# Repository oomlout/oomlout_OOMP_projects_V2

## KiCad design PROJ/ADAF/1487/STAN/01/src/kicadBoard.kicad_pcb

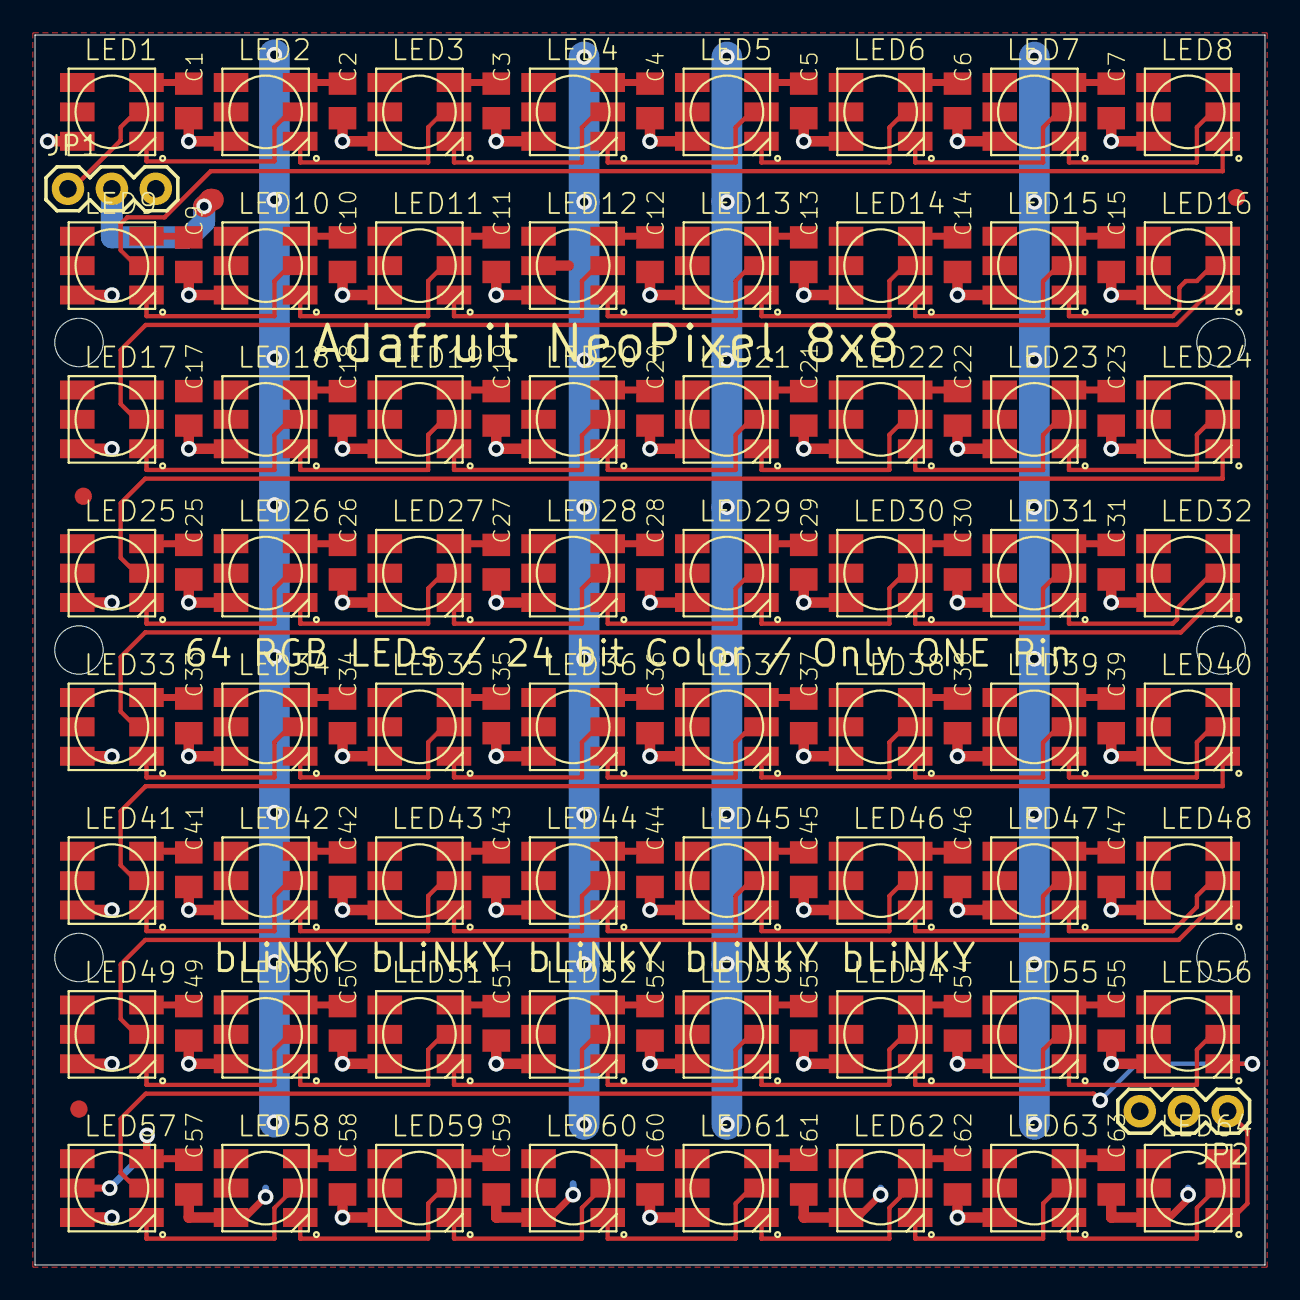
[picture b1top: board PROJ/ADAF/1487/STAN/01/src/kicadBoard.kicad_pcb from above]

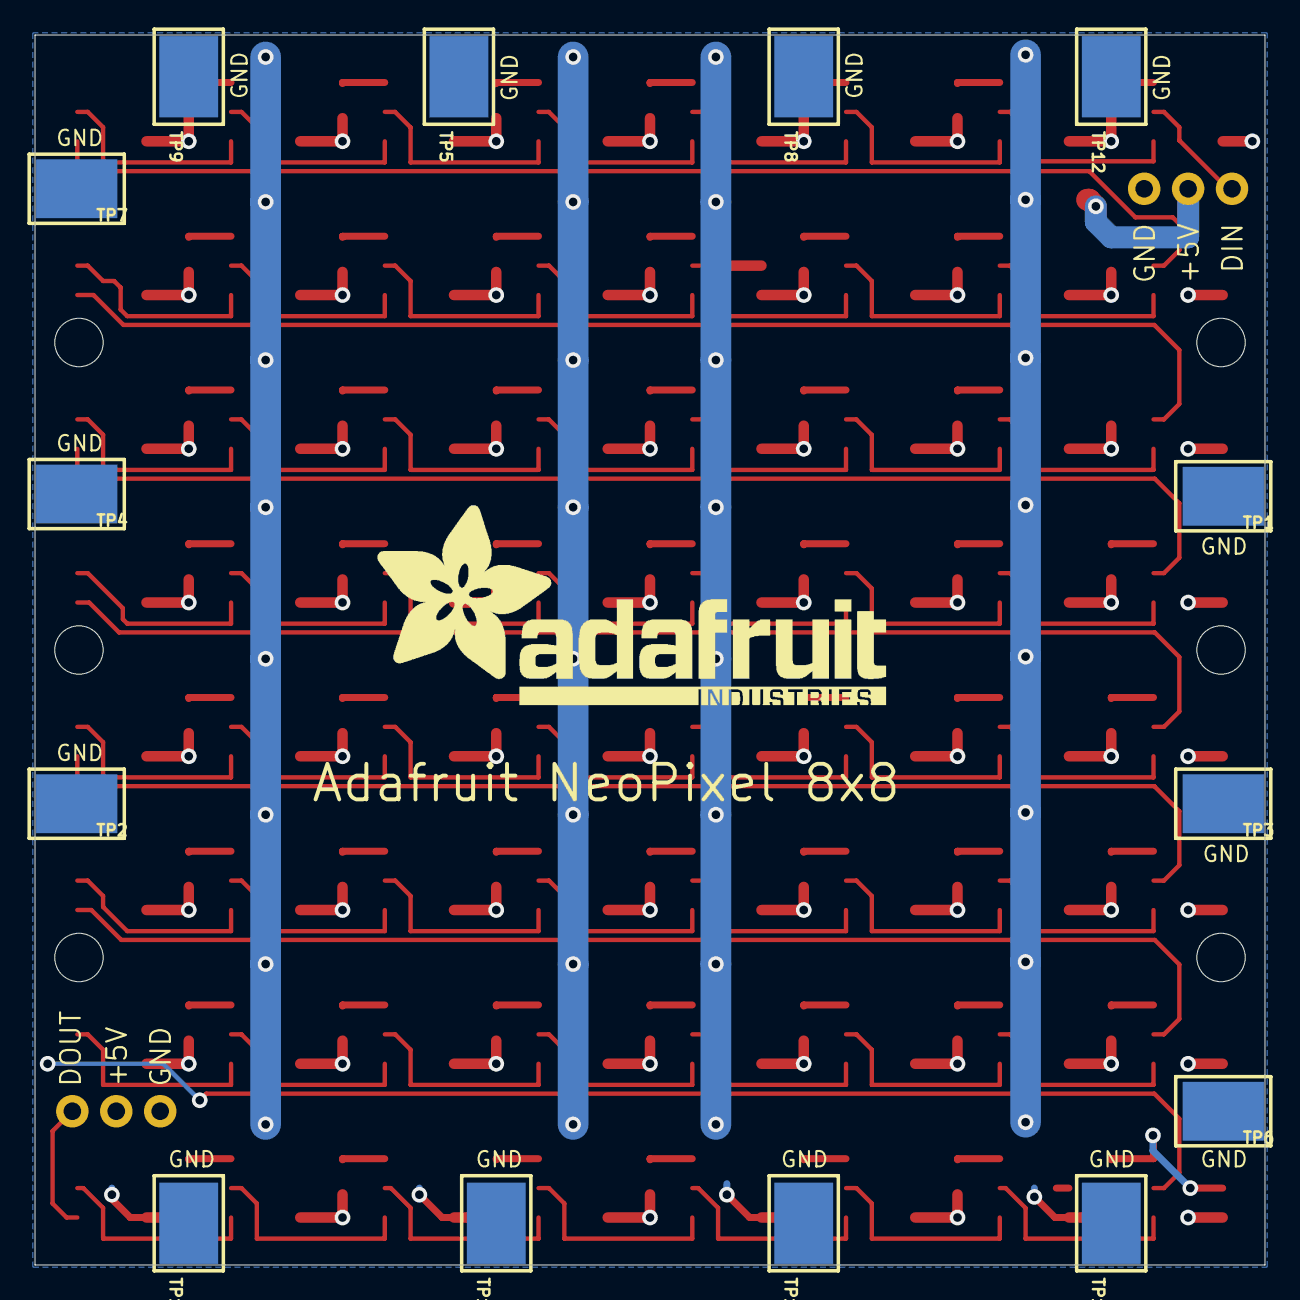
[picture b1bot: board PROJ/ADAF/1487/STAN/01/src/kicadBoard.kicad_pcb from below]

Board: 2 copper layers, 71.1 x 71.1 mm, 146 parts (15 on the bottom side), 67 nets.

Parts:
@HOLE0, @HOLE1, @HOLE2, @HOLE3, @HOLE4, @HOLE5: (no value)
C1, C2, C3, C4, C5, C6, C7, C9, C10, C11, C12, C13, C14, C15, C17, C18, C19, C20, C21, C22, C23, C25, C26, C27, C28, C29, C30, C31, C33, C34, C35, C36, C37, C38, C39, C41, C42, C43, C44, C45, C46, C47, C49, C50, C51, C52, C53, C54, C55, C57, C58, C59, C60, C61, C62, C63: RCL_C0805K
FID1, FID2, FID3: FIDUCIAL""; FIDUCIAL_1MM
JP1, JP2: 1X03
LED1, LED2, LED3, LED4, LED5, LED6, LED7, LED8, LED9, LED10, LED11, LED12, LED13, LED14, LED15, LED16, LED17, LED18, LED19, LED20, LED21, LED22, LED23, LED24, LED25, LED26, LED27, LED28, LED29, LED30, LED31, LED32, LED33, LED34, LED35, LED36, LED37, LED38, LED39, LED40, LED41, LED42, LED43, LED44, LED45, LED46, LED47, LED48, LED49, LED50, LED51, LED52, LED53, LED54, LED55, LED56, LED57, LED58, LED59, LED60, LED61, LED62, LED63, LED64: WS28115050
TP1, TP2, TP3, TP4, TP5, TP6, TP7, TP8, TP9, TP10, TP11, TP12, TP13, TP14: TESTPOINT_SMT
U$1: ADAFRUIT_TEXT_30MM

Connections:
GND: C1.2, C2.2, C3.2, C4.2, C5.2, C6.2, C7.2, C9.2, C10.2, C11.2, C12.2, C13.2, C14.2, C15.2, C17.2, C18.2, C19.2, C20.2, C21.2, C22.2, C23.2, C25.2, C26.2, C27.2, C28.2, C29.2, C30.2, C31.2, C33.2, C34.2, C35.2, C36.2, C37.2, C38.2, C39.2, C41.2, C42.2, C43.2, C44.2, C45.2, C46.2, C47.2, C49.2, C50.2, C51.2, C52.2, C53.2, C54.2, C55.2, C57.2, C58.2, C59.2, C60.2, C61.2, C62.2, C63.2, JP1.3, JP2.3, LED1.VSS, LED2.VSS, LED3.VSS, LED4.VSS, LED5.VSS, LED6.VSS, LED7.VSS, LED8.VSS, LED9.VSS, LED10.VSS, LED11.VSS, LED12.VSS, LED13.VSS, LED14.VSS, LED15.VSS, LED16.VSS, LED17.VSS, LED18.VSS, LED19.VSS, LED20.VSS, LED21.VSS, LED22.VSS, LED23.VSS, LED24.VSS, LED25.VSS, LED26.VSS, LED27.VSS, LED28.VSS, LED29.VSS, LED30.VSS, LED31.VSS, LED32.VSS, LED33.VSS, LED34.VSS, LED35.VSS, LED36.VSS, LED37.VSS, LED38.VSS, LED39.VSS, LED40.VSS, LED41.VSS, LED42.VSS, LED43.VSS, LED44.VSS, LED45.VSS, LED46.VSS, LED47.VSS, LED48.VSS, LED49.VSS, LED50.VSS, LED51.VSS, LED52.VSS, LED53.VSS, LED54.VSS, LED55.VSS, LED56.VSS, LED57.VSS, LED58.VSS, LED59.VSS, LED60.VSS, LED61.VSS, LED62.VSS, LED63.VSS, LED64.VSS, TP1.P$1, TP2.P$1, TP3.P$1, TP4.P$1, TP5.P$1, TP6.P$1, TP7.P$1, TP8.P$1, TP9.P$1, TP10.P$1, TP11.P$1, TP12.P$1, TP13.P$1, TP14.P$1
unnamed: JP1.1, LED1.DI
unnamed: LED8.DO, LED9.DI
unnamed: LED16.DO, LED17.DI
unnamed: LED24.DO, LED25.DI
unnamed: LED40.DO, LED41.DI
unnamed: LED32.DO, LED33.DI
unnamed: LED48.DO, LED49.DI
unnamed: LED56.DO, LED57.DI
unnamed: JP2.1, LED64.DO
unnamed: LED17.DO, LED18.DI
unnamed: LED25.DO, LED26.DI
unnamed: LED26.DO, LED27.DI
unnamed: LED2.DO, LED3.DI
unnamed: LED3.DO, LED4.DI
unnamed: LED4.DO, LED5.DI
unnamed: LED5.DO, LED6.DI
unnamed: LED6.DO, LED7.DI
unnamed: LED7.DO, LED8.DI
unnamed: LED10.DO, LED11.DI
unnamed: LED11.DO, LED12.DI
unnamed: LED12.DO, LED13.DI
unnamed: LED13.DO, LED14.DI
unnamed: LED14.DO, LED15.DI
unnamed: LED15.DO, LED16.DI
unnamed: LED18.DO, LED19.DI
unnamed: LED19.DO, LED20.DI
unnamed: LED20.DO, LED21.DI
unnamed: LED21.DO, LED22.DI
unnamed: LED22.DO, LED23.DI
unnamed: LED23.DO, LED24.DI
unnamed: LED27.DO, LED28.DI
unnamed: LED28.DO, LED29.DI
unnamed: LED29.DO, LED30.DI
unnamed: LED30.DO, LED31.DI
unnamed: LED31.DO, LED32.DI
unnamed: LED1.DO, LED2.DI
unnamed: LED9.DO, LED10.DI
unnamed: LED49.DO, LED50.DI
unnamed: LED57.DO, LED58.DI
unnamed: LED58.DO, LED59.DI
unnamed: LED34.DO, LED35.DI
unnamed: LED35.DO, LED36.DI
unnamed: LED36.DO, LED37.DI
unnamed: LED37.DO, LED38.DI
unnamed: LED38.DO, LED39.DI
unnamed: LED39.DO, LED40.DI
unnamed: LED42.DO, LED43.DI
unnamed: LED43.DO, LED44.DI
unnamed: LED44.DO, LED45.DI
unnamed: LED45.DO, LED46.DI
unnamed: LED46.DO, LED47.DI
unnamed: LED47.DO, LED48.DI
unnamed: LED50.DO, LED51.DI
unnamed: LED51.DO, LED52.DI
unnamed: LED52.DO, LED53.DI
unnamed: LED53.DO, LED54.DI
unnamed: LED54.DO, LED55.DI
unnamed: LED55.DO, LED56.DI
unnamed: LED59.DO, LED60.DI
unnamed: LED60.DO, LED61.DI
unnamed: LED61.DO, LED62.DI
unnamed: LED62.DO, LED63.DI
unnamed: LED63.DO, LED64.DI
unnamed: LED33.DO, LED34.DI
unnamed: LED41.DO, LED42.DI
VDD: C1.1, C2.1, C3.1, C4.1, C5.1, C6.1, C7.1, C9.1, C10.1, C11.1, C12.1, C13.1, C14.1, C15.1, C17.1, C18.1, C19.1, C20.1, C21.1, C22.1, C23.1, C25.1, C26.1, C27.1, C28.1, C29.1, C30.1, C31.1, C33.1, C34.1, C35.1, C36.1, C37.1, C38.1, C39.1, C41.1, C42.1, C43.1, C44.1, C45.1, C46.1, C47.1, C49.1, C50.1, C51.1, C52.1, C53.1, C54.1, C55.1, C57.1, C58.1, C59.1, C60.1, C61.1, C62.1, C63.1, JP1.2, JP2.2, LED1.LEDVDD, LED1.VDD, LED2.LEDVDD, LED2.VDD, LED3.LEDVDD, LED3.VDD, LED4.LEDVDD, LED4.VDD, LED5.LEDVDD, LED5.VDD, LED6.LEDVDD, LED6.VDD, LED7.LEDVDD, LED7.VDD, LED8.LEDVDD, LED8.VDD, LED9.LEDVDD, LED9.VDD, LED10.LEDVDD, LED10.VDD, LED11.LEDVDD, LED11.VDD, LED12.LEDVDD, LED12.VDD, LED13.LEDVDD, LED13.VDD, LED14.LEDVDD, LED14.VDD, LED15.LEDVDD, LED15.VDD, LED16.LEDVDD, LED16.VDD, LED17.LEDVDD, LED17.VDD, LED18.LEDVDD, LED18.VDD, LED19.LEDVDD, LED19.VDD, LED20.LEDVDD, LED20.VDD, LED21.LEDVDD, LED21.VDD, LED22.LEDVDD, LED22.VDD, LED23.LEDVDD, LED23.VDD, LED24.LEDVDD, LED24.VDD, LED25.LEDVDD, LED25.VDD, LED26.LEDVDD, LED26.VDD, LED27.LEDVDD, LED27.VDD, LED28.LEDVDD, LED28.VDD, LED29.LEDVDD, LED29.VDD, LED30.LEDVDD, LED30.VDD, LED31.LEDVDD, LED31.VDD, LED32.LEDVDD, LED32.VDD, LED33.LEDVDD, LED33.VDD, LED34.LEDVDD, LED34.VDD, LED35.LEDVDD, LED35.VDD, LED36.LEDVDD, LED36.VDD, LED37.LEDVDD, LED37.VDD, LED38.LEDVDD, LED38.VDD, LED39.LEDVDD, LED39.VDD, LED40.LEDVDD, LED40.VDD, LED41.LEDVDD, LED41.VDD, LED42.LEDVDD, LED42.VDD, LED43.LEDVDD, LED43.VDD, LED44.LEDVDD, LED44.VDD, LED45.LEDVDD, LED45.VDD, LED46.LEDVDD, LED46.VDD, LED47.LEDVDD, LED47.VDD, LED48.LEDVDD, LED48.VDD, LED49.LEDVDD, LED49.VDD, LED50.LEDVDD, LED50.VDD, LED51.LEDVDD, LED51.VDD, LED52.LEDVDD, LED52.VDD, LED53.LEDVDD, LED53.VDD, LED54.LEDVDD, LED54.VDD, LED55.LEDVDD, LED55.VDD, LED56.LEDVDD, LED56.VDD, LED57.LEDVDD, LED57.VDD, LED58.LEDVDD, LED58.VDD, LED59.LEDVDD, LED59.VDD, LED60.LEDVDD, LED60.VDD, LED61.LEDVDD, LED61.VDD, LED62.LEDVDD, LED62.VDD, LED63.LEDVDD, LED63.VDD, LED64.LEDVDD, LED64.VDD

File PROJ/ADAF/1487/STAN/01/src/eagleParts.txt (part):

Partlist

Exported from boardEagle.brd at 05/08/2022 21:47

EAGLE Version 9.6.2 Copyright (c) 1988-2020 Autodesk, Inc.

Assembly variant: 

Part     Value          Package       Library       Position (inch)       Orientation

C1                      RCL_C0805K    neomatrix-8x8 (-1.05 1.25)          R270
C2                      RCL_C0805K    neomatrix-8x8 (-0.7 1.25)           R270
C3                      RCL_C0805K    neomatrix-8x8 (-0.35 1.25)          R270
C4                      RCL_C0805K    neomatrix-8x8 (0 1.25)              R270
C5                      RCL_C0805K    neomatrix-8x8 (0.35 1.25)           R270
C6                      RCL_C0805K    neomatrix-8x8 (0.7 1.25)            R270
C7                      RCL_C0805K    neomatrix-8x8 (1.05 1.25)           R270
C9                      RCL_C0805K    neomatrix-8x8 (-1.05 0.9)           R270
C10                     RCL_C0805K    neomatrix-8x8 (-0.7 0.9)            R270
C11                     RCL_C0805K    neomatrix-8x8 (-0.35 0.9)           R270
C12                     RCL_C0805K    neomatrix-8x8 (0 0.9)               R270
C13                     RCL_C0805K    neomatrix-8x8 (0.35 0.9)            R270
C14                     RCL_C0805K    neomatrix-8x8 (0.7 0.9)             R270
C15                     RCL_C0805K    neomatrix-8x8 (1.05 0.9)            R270
C17                     RCL_C0805K    neomatrix-8x8 (-1.05 0.55)          R270
C18                     RCL_C0805K    neomatrix-8x8 (-0.7 0.55)           R270
C19                     RCL_C0805K    neomatrix-8x8 (-0.35 0.55)          R270
C20                     RCL_C0805K    neomatrix-8x8 (0 0.55)              R270
C21                     RCL_C0805K    neomatrix-8x8 (0.35 0.55)           R270
C22                     RCL_C0805K    neomatrix-8x8 (0.7 0.55)            R270
C23                     RCL_C0805K    neomatrix-8x8 (1.05 0.55)           R270
C25                     RCL_C0805K    neomatrix-8x8 (-1.05 0.2)           R270
C26                     RCL_C0805K    neomatrix-8x8 (-0.7 0.2)            R270
C27                     RCL_C0805K    neomatrix-8x8 (-0.35 0.2)           R270
C28                     RCL_C0805K    neomatrix-8x8 (0 0.2)               R270
C29                     RCL_C0805K    neomatrix-8x8 (0.35 0.2)            R270
C30                     RCL_C0805K    neomatrix-8x8 (0.7 0.2)             R270
C31                     RCL_C0805K    neomatrix-8x8 (1.05 0.2)            R270
C33                     RCL_C0805K    neomatrix-8x8 (-1.05 -0.15)         R270
C34                     RCL_C0805K    neomatrix-8x8 (-0.7 -0.15)          R270
C35                     RCL_C0805K    neomatrix-8x8 (-0.35 -0.15)         R270
C36                     RCL_C0805K    neomatrix-8x8 (0 -0.15)             R270
C37                     RCL_C0805K    neomatrix-8x8 (0.35 -0.15)          R270
C38                     RCL_C0805K    neomatrix-8x8 (0.7 -0.15)           R270
C39                     RCL_C0805K    neomatrix-8x8 (1.05 -0.15)          R270
C41                     RCL_C0805K    neomatrix-8x8 (-1.05 -0.5)          R270
C42                     RCL_C0805K    neomatrix-8x8 (-0.7 -0.5)           R270
C43                     RCL_C0805K    neomatrix-8x8 (-0.35 -0.5)          R270
C44                     RCL_C0805K    neomatrix-8x8 (0 -0.5)              R270
C45                     RCL_C0805K    neomatrix-8x8 (0.35 -0.5)           R270
C46                     RCL_C0805K    neomatrix-8x8 (0.7 -0.5)            R270
C47                     RCL_C0805K    neomatrix-8x8 (1.05 -0.5)           R270
C49                     RCL_C0805K    neomatrix-8x8 (-1.05 -0.85)         R270
C50                     RCL_C0805K    neomatrix-8x8 (-0.7 -0.85)          R270
C51                     RCL_C0805K    neomatrix-8x8 (-0.35 -0.85)         R270
C52                     RCL_C0805K    neomatrix-8x8 (0 -0.85)             R270
C53                     RCL_C0805K    neomatrix-8x8 (0.35 -0.85)          R270
C54                     RCL_C0805K    neomatrix-8x8 (0.7 -0.85)           R270
C55                     RCL_C0805K    neomatrix-8x8 (1.05 -0.85)          R270
C57                     RCL_C0805K    neomatrix-8x8 (-1.05 -1.2)          R270
C58                     RCL_C0805K    neomatrix-8x8 (-0.7 -1.2)           R270
C59                     RCL_C0805K    neomatrix-8x8 (-0.35 -1.2)          R270
C60                     RCL_C0805K    neomatrix-8x8 (0 -1.2)              R270
C61                     RCL_C0805K    neomatrix-8x8 (0.35 -1.2)           R270
C62                     RCL_C0805K    neomatrix-8x8 (0.7 -1.2)            R270
C63                     RCL_C0805K    neomatrix-8x8 (1.05 -1.2)           R270
FID1     FIDUCIAL""     FIDUCIAL_1MM  microbuilder  (1.335 1.03)          R0
FID2     FIDUCIAL""     FIDUCIAL_1MM  microbuilder  (-1.29 0.35)          R0
FID3     FIDUCIAL""     FIDUCIAL_1MM  microbuilder  (-1.3 -1.045)         R0
JP1                     1X03          neomatrix-8x8 (-1.325 1.05)         R0
JP2                     1X03          neomatrix-8x8 (1.315 -1.05)         R180
LED1     WS28115050     WS28115050    neomatrix-8x8 (-1.225 1.225)        R0
LED2     WS28115050     WS28115050    neomatrix-8x8 (-0.875 1.225)        R0
LED3     WS28115050     WS28115050    neomatrix-8x8 (-0.525 1.225)        R0
LED4     WS28115050     WS28115050    neomatrix-8x8 (-0.175 1.225)        R0
LED5     WS28115050     WS28115050    neomatrix-8x8 (0.175 1.225)         R0
LED6     WS28115050     WS28115050    neomatrix-8x8 (0.525 1.225)         R0
LED7     WS28115050     WS28115050    neomatrix-8x8 (0.875 1.225)         R0
LED8     WS28115050     WS28115050    neomatrix-8x8 (1.225 1.225)         R0
LED9     WS28115050     WS28115050    neomatrix-8x8 (-1.225 0.875)        R0
LED10    WS28115050     WS28115050    neomatrix-8x8 (-0.875 0.875)        R0
LED11    WS28115050     WS28115050    neomatrix-8x8 (-0.525 0.875)        R0
LED12    WS28115050     WS28115050    neomatrix-8x8 (-0.175 0.875)        R0
LED13    WS28115050     WS28115050    neomatrix-8x8 (0.175 0.875)         R0
LED14    WS28115050     WS28115050    neomatrix-8x8 (0.525 0.875)         R0
LED15    WS28115050     WS28115050    neomatrix-8x8 (0.875 0.875)         R0
LED16    WS28115050     WS28115050    neomatrix-8x8 (1.225 0.875)         R0
LED17    WS28115050     WS28115050    neomatrix-8x8 (-1.225 0.525)        R0
LED18    WS28115050     WS28115050    neomatrix-8x8 (-0.875 0.525)        R0
LED19    WS28115050     WS28115050    neomatrix-8x8 (-0.525 0.525)        R0
LED20    WS28115050     WS28115050    neomatrix-8x8 (-0.175 0.525)        R0
LED21    WS28115050     WS28115050    neomatrix-8x8 (0.175 0.525)         R0
LED22    WS28115050     WS28115050    neomatrix-8x8 (0.525 0.525)         R0
LED23    WS28115050     WS28115050    neomatrix-8x8 (0.875 0.525)         R0
LED24    WS28115050     WS28115050    neomatrix-8x8 (1.225 0.525)         R0
LED25    WS28115050     WS28115050    neomatrix-8x8 (-1.225 0.175)        R0
LED26    WS28115050     WS28115050    neomatrix-8x8 (-0.875 0.175)        R0
LED27    WS28115050     WS28115050    neomatrix-8x8 (-0.525 0.175)        R0
LED28    WS28115050     WS28115050    neomatrix-8x8 (-0.175 0.175)        R0
LED29    WS28115050     WS28115050    neomatrix-8x8 (0.175 0.175)         R0
LED30    WS28115050     WS28115050    neomatrix-8x8 (0.525 0.175)         R0
LED31    WS28115050     WS28115050    neomatrix-8x8 (0.875 0.175)         R0
LED32    WS28115050     WS28115050    neomatrix-8x8 (1.225 0.175)         R0
LED33    WS28115050     WS28115050    neomatrix-8x8 (-1.225 -0.175)       R0
LED34    WS28115050     WS28115050    neomatrix-8x8 (-0.875 -0.175)       R0
LED35    WS28115050     WS28115050    neomatrix-8x8 (-0.525 -0.175)       R0
LED36    WS28115050     WS28115050    neomatrix-8x8 (-0.175 -0.175)       R0
LED37    WS28115050     WS28115050    neomatrix-8x8 (0.175 -0.175)        R0
LED38    WS28115050     WS28115050    neomatrix-8x8 (0.525 -0.175)        R0
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
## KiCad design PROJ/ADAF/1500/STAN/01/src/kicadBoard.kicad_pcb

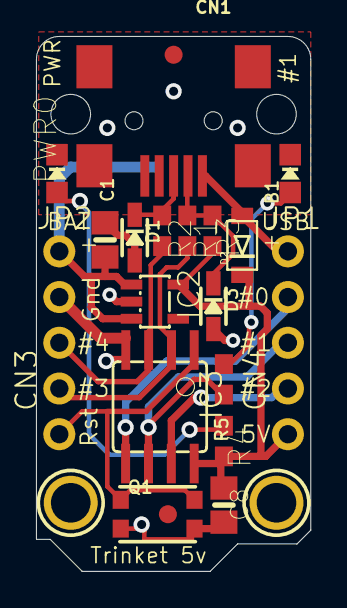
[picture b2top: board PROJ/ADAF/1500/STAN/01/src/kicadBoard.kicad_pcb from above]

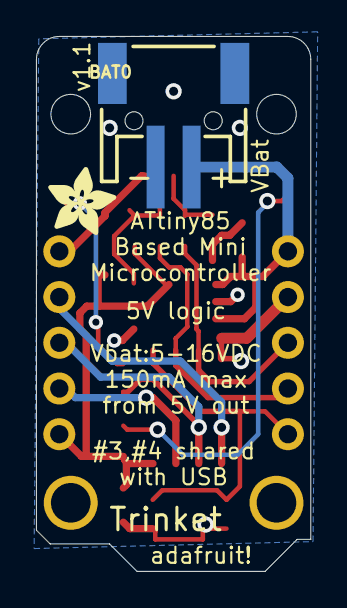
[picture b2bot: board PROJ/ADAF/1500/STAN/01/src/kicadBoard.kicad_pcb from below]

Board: 16 copper layers, 15.2 x 29.7 mm, 28 parts (2 on the bottom side), 14 nets.

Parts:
@HOLE0, @HOLE1: (no value)
B1: red; CHIPLED_0805_NOOUTLINE
BAT0: JSTPH2
C1, C8: 10uF; 0805-NO
CN1: USB-MINIB
CN3, CN4: 1X4-CLEANBIG; 1X04-CLEANBIG
D1, D3: 3.6V; SOD-323
D2: SCHOTTKY; SOD-123FL
IC2: MIC5225-5.0v; SOT23-5L
IC3: ATTINY85-20S; SOIC8
JP1, JP2: 1X01-CLEANBIG
PWR0: green; CHIPLED_0805_NOOUTLINE
Q1: reset; BTN_KMR2_4.6X2.8
R1, R2: 68 (0603); 0603-NO
R3: 1.5K (0603); 0603-NO
R4, R5: 470 (0603); 0603-NO
U$1, U$6: FIDUCIAL; FIDUCIAL_1MM
U$5: ADAFRUIT_3.5MM
U$8, U$9: MOUNTINGHOLE2.0; MOUNTINGHOLE_2.0_PLATED

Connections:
+5V: C8.1, CN4.1, D2.C, IC2.5, IC3.8, R3.2, R4.2
B0: CN4.4, IC3.5
B1: CN4.3, IC3.6, R5.2
B2: CN4.2, IC3.7
B3: CN3.2, IC3.2, R1.2
B4: CN3.3, IC3.3, R2.2
GND: B1.C, BAT0.1, C1.2, C8.2, CN1.GND, CN1.GND1, CN1.GND2, CN1.GND3, CN1.GND4, CN3.4, D1.A, D3.A, IC2.2, IC3.4, PWR0.C, Q1.B, Q1.B'
unnamed: B1.A, R5.1
unnamed: CN1.D+, D1.C, R2.1
unnamed: CN1.D-, D3.C, R1.1, R3.1
unnamed: PWR0.A, R4.1
RESET: CN3.1, IC3.1, Q1.A, Q1.A'
VBAT: BAT0.2, C1.1, IC2.1, IC2.3, JP2.1
VBUS: CN1.VBUS, D2.A, JP1.1

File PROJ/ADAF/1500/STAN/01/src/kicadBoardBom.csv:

"Id";"Designator";"Package";"Quantity";"Designation";"Supplier and ref";
1;"R3";"0603-NO";1;"1.5K (0603)";;;
2;"U$1,U$6";"FIDUCIAL_1MM";2;"FIDUCIAL";;;
3;"R4,R5";"0603-NO";2;"470 (0603)";;;
4;"CN1";"USB-MINIB";1;"";;;
5;"@HOLE1,@HOLE0";"";2;"";;;
6;"D3,D1";"SOD-323";2;"3.6V";;;
7;"CN4,CN3";"1X04-CLEANBIG";2;"1X4-CLEANBIG";;;
8;"PWR0";"CHIPLED_0805_NOOUTLINE";1;"green";;;
9;"IC2";"SOT23-5L";1;"MIC5225-5.0v";;;
10;"B1";"CHIPLED_0805_NOOUTLINE";1;"red";;;
11;"U$9,U$8";"MOUNTINGHOLE_2.0_PLATED";2;"MOUNTINGHOLE2.0";;;
12;"R1,R2";"0603-NO";2;"68 (0603)";;;
13;"C1,C8";"0805-NO";2;"10uF";;;
14;"IC3";"SOIC8";1;"ATTINY85-20S";;;
15;"JP1,JP2";"1X01-CLEANBIG";2;"";;;
16;"Q1";"BTN_KMR2_4.6X2.8";1;"reset";;;
17;"D2";"SOD-123FL";1;"SCHOTTKY";;;
18;"BAT0";"JSTPH2";1;"";;;
19;"U$5";"ADAFRUIT_3.5MM";1;"";;;

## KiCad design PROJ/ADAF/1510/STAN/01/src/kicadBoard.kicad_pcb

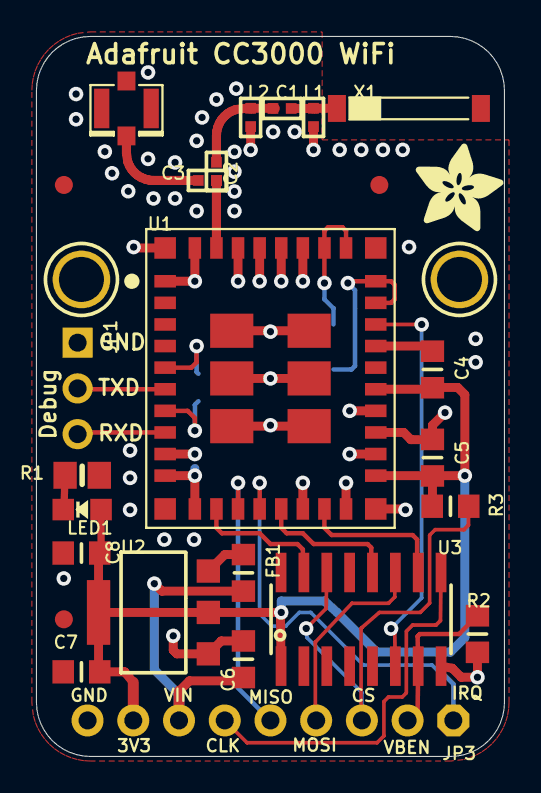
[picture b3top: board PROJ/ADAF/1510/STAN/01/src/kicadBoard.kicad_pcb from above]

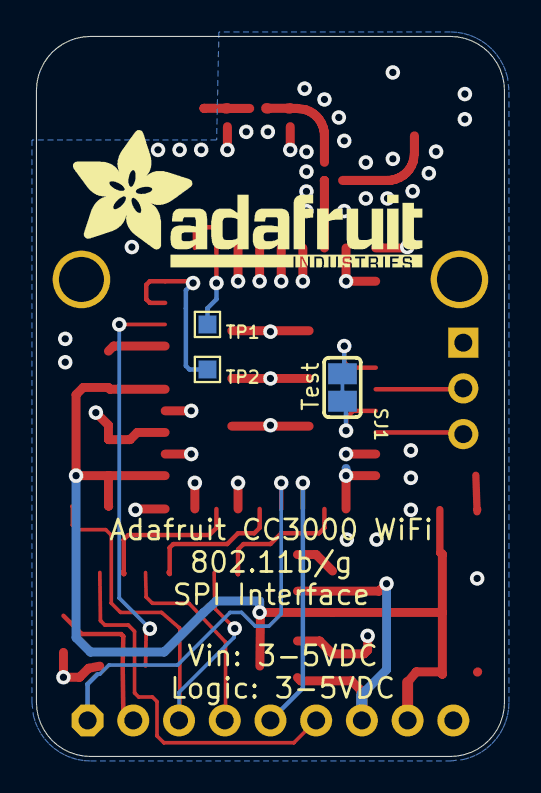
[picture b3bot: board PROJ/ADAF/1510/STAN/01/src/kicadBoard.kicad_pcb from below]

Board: 2 copper layers, 26.0 x 40.0 mm, 32 parts (4 on the bottom side), 25 nets.

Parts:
C1: 2.2pF; _0402
C2: 10pF; _0402
C3: DNC_10pF; _0402
C4, C5: 1µF; _0805MP
C6, C7, C8: 10µF; _0805MP
FB1: _0805MP
FID1, FID2, FID3: FIDUCIAL""; FIDUCIAL_1MM
JP1: 1X03_ROUND
JP3: 1X09_ROUND_70
L1: DNP; _0402
L2: 2.2nH; _0402
LED1: green; CHIPLED_0805_NOOUTLINE
R1: 470; 0805-NO
R2, R3: 10K; _0805MP
SJ1: TESTMODE; SOLDERJUMPER_CLOSEDWIRE
TP1: SCL; TESTPOINT_PAD_1MM
TP2: SDA; TESTPOINT_PAD_1MM
U1: CC3000MOD
U2: SOT223-R
U3: 74HC4050D; SOIC16
U$8: ADAFRUIT_5MM
U$24, U$34: MOUNTINGHOLE2.5; MOUNTINGHOLE_2.5_PLATED
U$35: U.FL
U$36: ADAFRUIT_TEXT_20MM
X1: 2500AT44M0400E; ANT_2500AT44M0400

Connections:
GND: C4.2, C5.2, C6.2, C7.2, C8.2, JP1.1, JP3.9, L1.1, L2.1, R1.1, R2.1, U1.1, U1.9, U1.10, U1.11, U1.16, U1.18, U1.20, U1.21, U1.22, U1.25, U1.31, U1.32, U1.33, U1.34, U1.36, U1.37, U1.38, U1.39, U1.40, U1.41, U1.42, U1.43, U1.44, U1.45, U1.46, U2.1, U3.8, U$35.P$1, U$35.P$2
unnamed: C1.2, L1.2, X1.FEED
unnamed: C1.1, C2.1, L2.2
unnamed: C3.2, U$35.P$3
unnamed: C2.2, C3.1, U1.35
unnamed: SJ1.2, U1.5
unnamed: SJ1.1, U1.7
unnamed: LED1.C, R1.2
unnamed: FB1.2, U2.3
RXD_3V: JP1.3, U1.8
SCL_3V: TP1.P$1, U1.29, U1.30
SDA_3V: TP2.P$1, U1.27, U1.28
SPI_CLK_3V: U1.17, U3.10
SPI_CLK_5V: JP3.6, U3.9
SPI_CS_3V: U1.12, U3.15
SPI_CS_5V: JP3.3, R3.2, U3.14
SPI_IRQ_3V: JP3.1, U1.14
SPI_MISO_3V: JP3.5, U1.13
SPI_MOSI_3V: U1.15, U3.12
SPI_MOSI_5V: JP3.4, U3.11
TXD_3V: JP1.2, U1.6
VBAT: C4.1, C5.1, C7.1, C8.1, JP3.8, LED1.A, R3.1, U1.19, U1.23, U2.2, U2.4, U3.1
VBAT_EN_3V: U1.26, U3.6
VBAT_EN_5V: JP3.2, R2.2, U3.7
VIN: C6.1, FB1.1, JP3.7

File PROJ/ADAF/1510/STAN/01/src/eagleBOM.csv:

"Part";"Value";"Device";"Package";"Description";"BOM";
"C1";"2.2pF";"CAP_CERAMIC_0402";"_0402";"Ceramic Capacitors";"";
"C2";"10pF";"CAP_CERAMIC_0402";"_0402";"Ceramic Capacitors";"";
"C3";"DNC_10pF";"CAP_CERAMIC_0402";"_0402";"Ceramic Capacitors";"";
"C4";"1µF";"CAP_CERAMIC_0805MP";"_0805MP";"Ceramic Capacitors";"";
"C5";"1µF";"CAP_CERAMIC_0805MP";"_0805MP";"Ceramic Capacitors";"";
"C6";"10µF";"CAP_CERAMIC_0805MP";"_0805MP";"Ceramic Capacitors";"";
"C7";"10µF";"CAP_CERAMIC_0805MP";"_0805MP";"Ceramic Capacitors";"";
"C8";"10µF";"CAP_CERAMIC_0805MP";"_0805MP";"Ceramic Capacitors";"";
"FB1";"";"FERRITE_0805MP";"_0805MP";"Ferrite Bead";"";
"FID1";"FIDUCIAL""";"FIDUCIAL""";"FIDUCIAL_1MM";"Fiducial Alignment Points";"EXCLUDE";
"FID2";"FIDUCIAL""";"FIDUCIAL""";"FIDUCIAL_1MM";"Fiducial Alignment Points";"EXCLUDE";
"FID3";"FIDUCIAL""";"FIDUCIAL""";"FIDUCIAL_1MM";"Fiducial Alignment Points";"EXCLUDE";
"JP1";"";"HEADER-1X3ROUND";"1X03_ROUND";"PIN HEADER";"";
"JP3";"";"HEADER-1X970MIL";"1X09_ROUND_70";"PIN HEADER";"";
"L1";"DNP";"INDUCTOR_0402";"_0402";"Inductors";"";
"L2";"2.2nH";"INDUCTOR_0402";"_0402";"Inductors";"";
"LED1";"green";"LED0805_NOOUTLINE";"CHIPLED_0805_NOOUTLINE";"LED";"";
"R1";"470";"RESISTOR0805_NOOUTLINE";"0805-NO";"Resistors";"";
"R2";"10K";"RESISTOR_0805MP";"_0805MP";"Resistors";"";
"R3";"10K";"RESISTOR_0805MP";"_0805MP";"Resistors";"";
"SJ1";"TESTMODE";"SOLDERJUMPER_CLOSED";"SOLDERJUMPER_CLOSEDWIRE";"Solder Jumper - Closed";"";
"TP1";"SCL";"TESTPOINTPAD1MM";"TESTPOINT_PAD_1MM";"Test Point";"";
"TP2";"SDA";"TESTPOINTPAD1MM";"TESTPOINT_PAD_1MM";"Test Point";"";
"U$24";"MOUNTINGHOLE2.5";"MOUNTINGHOLE2.5";"MOUNTINGHOLE_2.5_PLATED";"Mounting Hole";"EXCLUDE";
"U$34";"MOUNTINGHOLE2.5";"MOUNTINGHOLE2.5";"MOUNTINGHOLE_2.5_PLATED";"Mounting Hole";"EXCLUDE";
"U$35";"U.FL";"U.FL";"U.FL";"U.FL Antenna Connector";"";
"U1";"CC3000MOD";"CC3000MOD";"CC3000MOD";"CC3000MOD Wifi Module";"";
"U2";"";"VREG_SOT223";"SOT223-R";"SOT-223 Fixed Voltage Regulators";"";
"U3";"74HC4050D";"74HC4050D";"SOIC16";"6-channel level shifter";"";
"X1";"2500AT44M0400E";"ANTENNA_JOHANSON_2500AT44M0400";"ANT_2500AT44M0400";"Johanson 2.3-2.7 GHz Chip Antenna";"";

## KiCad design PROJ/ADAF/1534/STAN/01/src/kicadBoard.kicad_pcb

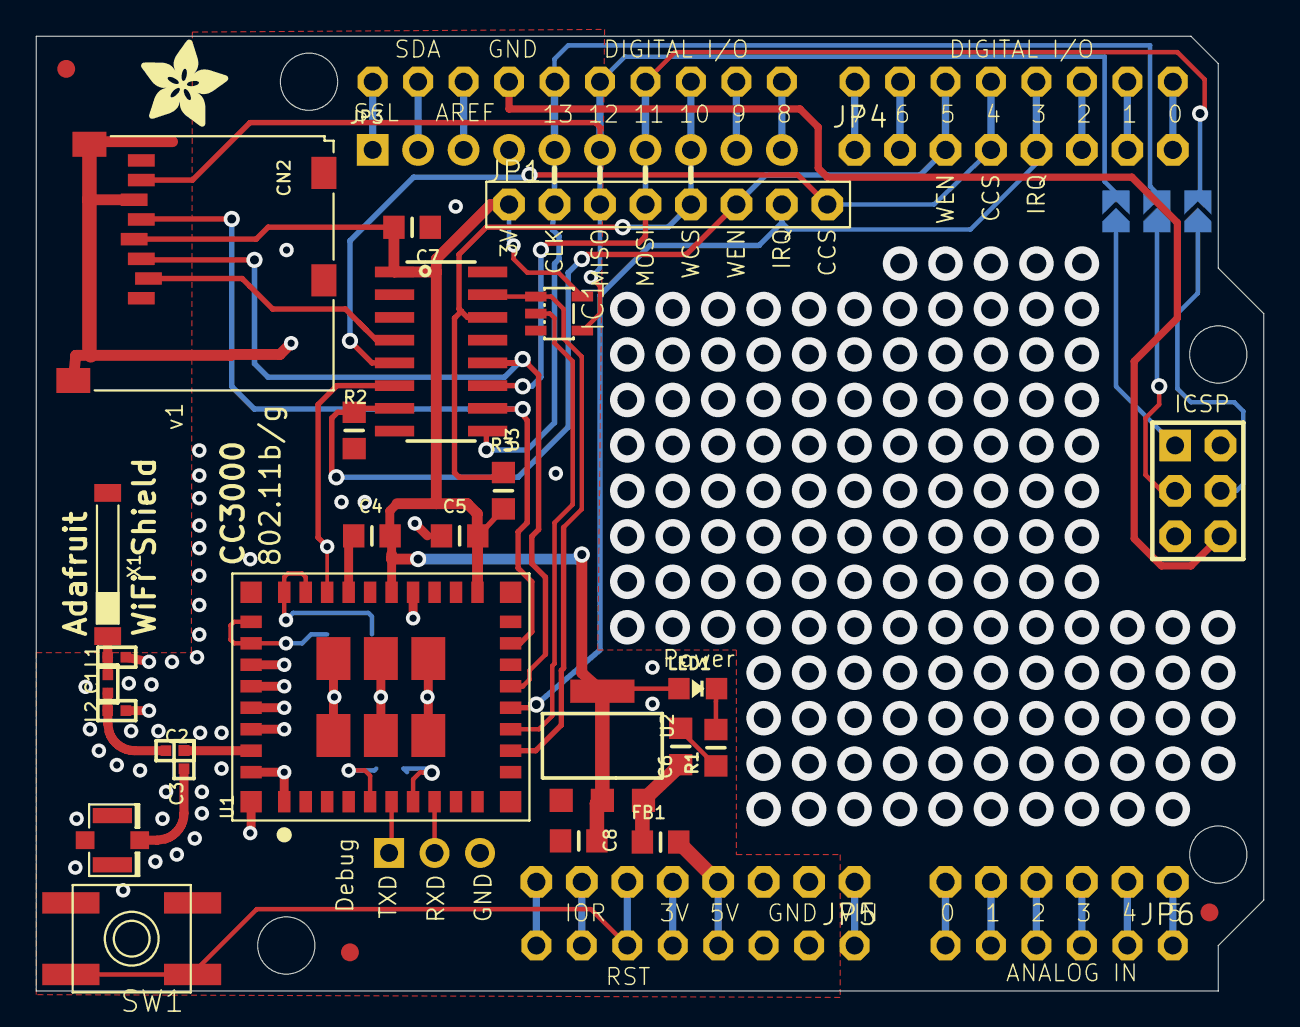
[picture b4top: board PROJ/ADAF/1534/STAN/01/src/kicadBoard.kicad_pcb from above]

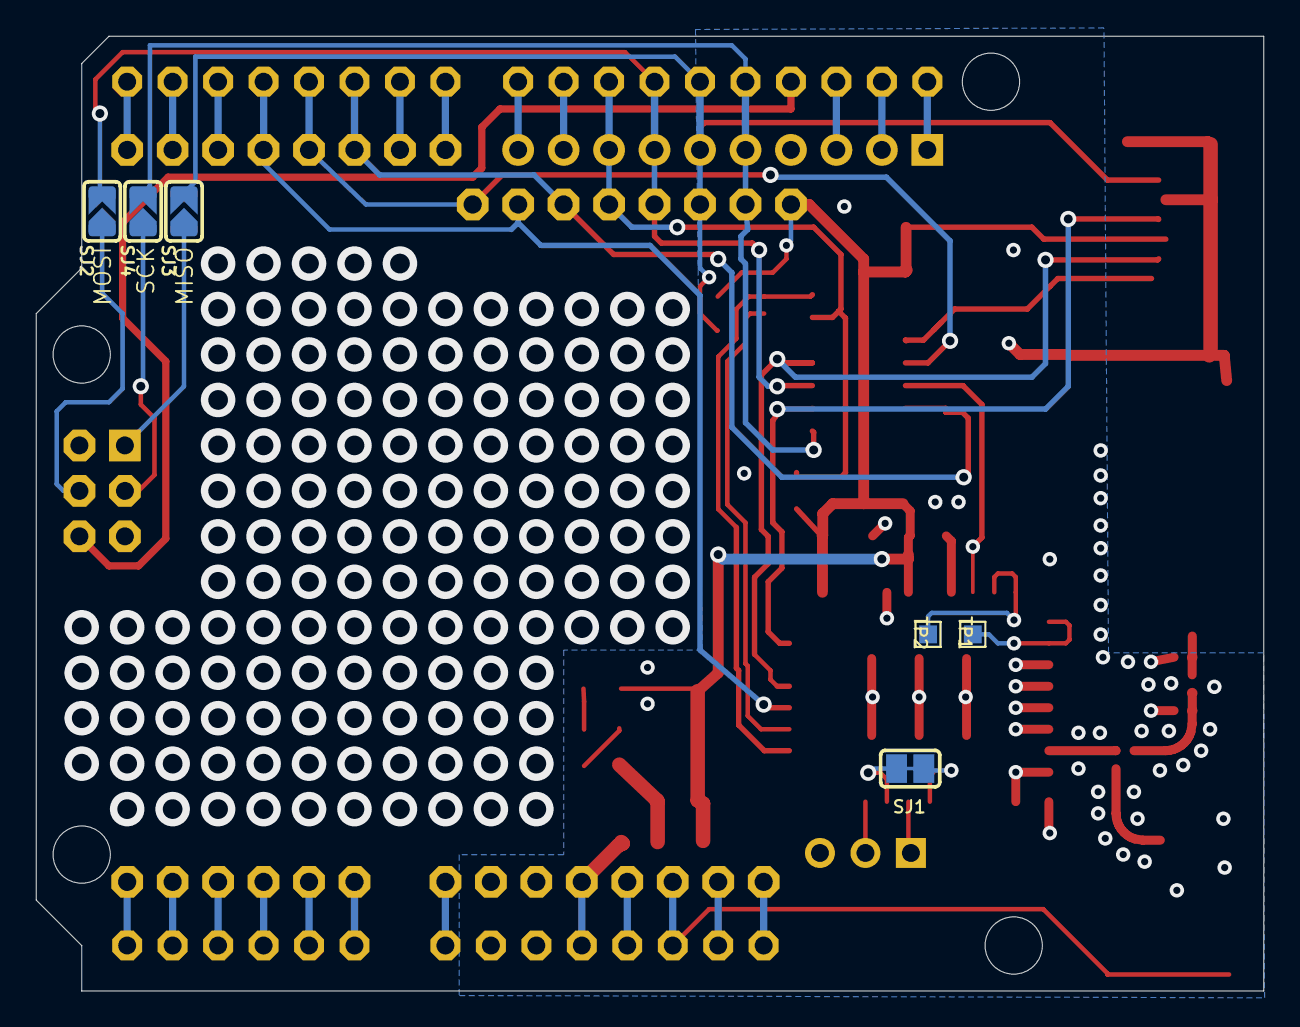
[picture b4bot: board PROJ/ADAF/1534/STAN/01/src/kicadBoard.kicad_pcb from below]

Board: 2 copper layers, 68.6 x 53.3 mm, 44 parts (6 on the bottom side), 52 nets.

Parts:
@HOLE0, @HOLE1, @HOLE2, @HOLE3: (no value)
C1: 2.2pF; _0402
C2: 10pF; _0402
C3: DNC_10pF; _0402
C4, C5: 1µF; _0805MP
C6, C7, C8: 10µF; _0805MP
CN2: microSD; MICROSD
FB1: Ferrite; _0805MP
FID1, FID2, FID3: FIDUCIAL""; FIDUCIAL_1MM
IC1: 74AHC1G125; SOT23-5L
JP1: 1X08-BIG
JP2: 1X03_ROUND
JP3: 1X10_ROUND70
JP4, JP5: 1X08-CLEANBIG
JP6: 1X06-CLEANBIG
L1: DNP; _0402
L2: 2.2nH; _0402
LED1: green; CHIPLED_0805_NOOUTLINE
R1: 470 ohm; _0805MP
R2, R3: 10K; _0805MP
SJ1: TESTMODE; SOLDERJUMPER_CLOSEDWIRE
SJ2: MOSIHW; SOLDERJUMPER_ARROW_NOPASTE
SJ3: MISOHW; SOLDERJUMPER_ARROW_NOPASTE
SJ4: SCKHW; SOLDERJUMPER_ARROW_NOPASTE
SW1: SPST_TACT-EVQQ2; EVQ-Q2
TP1: SCL; TESTPOINT_PAD_1MM
TP2: SDA; TESTPOINT_PAD_1MM
U1: CC3000MOD
U2: LT1117-3v; SOT223-R
U3: 74HC4050D; SOIC16
U$8: ADAFRUIT_5MM
U$35: U.FL
U$36: ARDUINO_R3_ICSP; ARDUINOR3_ICSP
X1: 2450AT18B100; ANT_2500AT44M0400

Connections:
3.3V: C4.1, C5.1, C7.1, C8.1, CN2.4, IC1.5, JP1.1, LED1.A, R3.1, U1.19, U1.23, U2.2, U2.4, U3.1
+5V: FB1.1, JP5.4, U$36.5V
GND: C4.2, C5.2, C6.2, C7.2, C8.2, CN2.6, CN2.MT1, CN2.MT2, IC1.3, JP2.3, JP3.4, JP5.2, JP5.3, L1.1, L2.1, R1.1, R2.1, SW1.A, SW1.A', U1.1, U1.9, U1.10, U1.11, U1.16, U1.18, U1.20, U1.21, U1.22, U1.25, U1.31, U1.32, U1.33, U1.34, U1.36, U1.37, U1.38, U1.39, U1.40, U1.41, U1.42, U1.43, U1.44, U1.45, U1.46, U2.1, U3.8, U$35.P$1, U$35.P$2, U$36.GND, U$36.GND@1, U$36.GND@2, U$36.GND@3
unnamed: C1.2, L1.2, X1.FEED
unnamed: C1.1, C2.1, L2.2
unnamed: C3.2, U$35.P$3
unnamed: C2.2, C3.1, U1.35
unnamed: SJ1.2, U1.5
unnamed: SJ1.1, U1.7
unnamed: JP3.1, U$36.SCL
unnamed: JP3.2, U$36.SDA
unnamed: C6.1, FB1.2, U2.3
unnamed: JP3.3, U$36.AREF
unnamed: JP5.6, SW1.B, SW1.B', U$36.RESET
unnamed: IC1.2, U1.13
unnamed: JP3.9, U$36.D9
unnamed: JP3.10, U$36.D8
unnamed: JP4.1, U$36.D7
unnamed: JP4.2, U$36.D6
unnamed: JP4.6, U$36.D2
unnamed: JP4.7, U$36.D1
unnamed: JP4.8, U$36.D0
unnamed: JP5.1, U$36.VIN
unnamed: JP5.5, U$36.3V
unnamed: JP5.7, U$36.IOREF
unnamed: JP5.8, U$36.RESERVED
unnamed: JP6.1, U$36.A5
unnamed: JP6.2, U$36.A4
unnamed: JP6.3, U$36.A3
unnamed: JP6.4, U$36.A2
unnamed: JP6.5, U$36.A1
unnamed: JP6.6, U$36.A0
unnamed: LED1.C, R1.2
unnamed: SJ2.1, U$36.MOSI
unnamed: SJ4.1, U$36.SCK
unnamed: SJ3.1, U$36.MISO
RXD_3V: JP2.2, U1.8
SCL_3V: TP1.P$1, U1.29, U1.30
SDA_3V: TP2.P$1, U1.27, U1.28
SD_CS_3V: CN2.2, U3.4
SD_CS_5V: JP1.8, JP4.4, U3.5, U$36.D4
SPI_CLK_3V: CN2.5, U1.17, U3.10
SPI_CLK_5V: JP1.2, JP3.5, SJ4.2, U3.9, U$36.D13
SPI_CS_3V: IC1.1, U1.12, U3.15
SPI_CS_5V: JP1.5, JP3.8, R3.2, U3.14, U$36.D10
SPI_IRQ_3V: JP1.7, JP4.5, U1.14, U$36.D3
SPI_MISO_3V: CN2.7, IC1.4, JP1.3, JP3.6, SJ3.2, U$36.D12
SPI_MOSI_3V: CN2.3, U1.15, U3.12
SPI_MOSI_5V: JP1.4, JP3.7, SJ2.2, U3.11, U$36.D11
TXD_3V: JP2.1, U1.6
VBAT_EN_3V: U1.26, U3.6
VBAT_EN_5V: JP1.6, JP4.3, R2.2, U3.7, U$36.D5

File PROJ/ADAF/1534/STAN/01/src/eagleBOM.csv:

"Part";"Value";"Device";"Package";"Description";"BOM";
"C1";"2.2pF";"CAP_CERAMIC_0402";"_0402";"Ceramic Capacitors";"";
"C2";"10pF";"CAP_CERAMIC_0402";"_0402";"Ceramic Capacitors";"";
"C3";"DNC_10pF";"CAP_CERAMIC_0402";"_0402";"Ceramic Capacitors";"";
"C4";"1µF";"CAP_CERAMIC_0805MP";"_0805MP";"Ceramic Capacitors";"";
"C5";"1µF";"CAP_CERAMIC_0805MP";"_0805MP";"Ceramic Capacitors";"";
"C6";"10µF";"CAP_CERAMIC_0805MP";"_0805MP";"Ceramic Capacitors";"";
"C7";"10µF";"CAP_CERAMIC_0805MP";"_0805MP";"Ceramic Capacitors";"";
"C8";"10µF";"CAP_CERAMIC_0805MP";"_0805MP";"Ceramic Capacitors";"";
"CN2";"microSD";"MICROSD";"MICROSD";"MicroSD/Transflash Card Holder with SPI pinout";"";
"FB1";"Ferrite";"FERRITE_0805MP";"_0805MP";"Ferrite Bead";"";
"FID1";"FIDUCIAL""";"FIDUCIAL""";"FIDUCIAL_1MM";"Fiducial Alignment Points";"EXCLUDE";
"FID2";"FIDUCIAL""";"FIDUCIAL""";"FIDUCIAL_1MM";"Fiducial Alignment Points";"EXCLUDE";
"FID3";"FIDUCIAL""";"FIDUCIAL""";"FIDUCIAL_1MM";"Fiducial Alignment Points";"EXCLUDE";
"IC1";"74AHC1G125";"74AHC1G125";"SOT23-5L";"";"";
"JP1";"";"PINHD-1X8BIG";"1X08-BIG";"PIN HEADER";"";
"JP2";"";"HEADER-1X3ROUND";"1X03_ROUND";"PIN HEADER";"";
"JP3";"";"HEADER-1X1070MIL";"1X10_ROUND70";"PIN HEADER";"";
"JP4";"";"PINHD-1X8CLEANBIG";"1X08-CLEANBIG";"PIN HEADER";"";
"JP5";"";"PINHD-1X8CLEANBIG";"1X08-CLEANBIG";"PIN HEADER";"";
"JP6";"";"PINHD-1X6CB";"1X06-CLEANBIG";"PIN HEADER";"";
"L1";"DNP";"INDUCTOR_0402";"_0402";"Inductors";"";
"L2";"2.2nH";"INDUCTOR_0402";"_0402";"Inductors";"";
"LED1";"green";"LED0805_NOOUTLINE";"CHIPLED_0805_NOOUTLINE";"LED";"";
"R1";"470 ohm";"RESISTOR_0805MP";"_0805MP";"Resistors";"";
"R2";"10K";"RESISTOR_0805MP";"_0805MP";"Resistors";"";
"R3";"10K";"RESISTOR_0805MP";"_0805MP";"Resistors";"";
"SJ1";"TESTMODE";"SOLDERJUMPER_CLOSED";"SOLDERJUMPER_CLOSEDWIRE";"Solder Jumper - Closed";"";
"SJ2";"MOSIHW";"SOLDERJUMPER";"SOLDERJUMPER_ARROW_NOPASTE";"SMD Solder JUMPER";"EXCLUDE";
"SJ3";"MISOHW";"SOLDERJUMPER";"SOLDERJUMPER_ARROW_NOPASTE";"SMD Solder JUMPER";"EXCLUDE";
"SJ4";"SCKHW";"SOLDERJUMPER";"SOLDERJUMPER_ARROW_NOPASTE";"SMD Solder JUMPER";"EXCLUDE";
"SW1";"SPST_TACT-EVQQ2";"SPST_TACT-EVQQ2";"EVQ-Q2";"SMT 6mm switch, EVQQ2 series";"";
"TP1";"SCL";"TESTPOINTPAD1MM";"TESTPOINT_PAD_1MM";"Test Point";"";
"TP2";"SDA";"TESTPOINTPAD1MM";"TESTPOINT_PAD_1MM";"Test Point";"";
"U$35";"U.FL";"U.FL";"U.FL";"U.FL Antenna Connector";"";
"U$36";"ARDUINO_R3_ICSP";"ARDUINO_R3_ICSP";"ARDUINOR3_ICSP";"";"";
"U1";"CC3000MOD";"CC3000MOD";"CC3000MOD";"CC3000MOD Wifi Module";"";
"U2";"LT1117-3v";"VREG_SOT223";"SOT223-R";"SOT-223 Fixed Voltage Regulators";"";
"U3";"74HC4050D";"74HC4050D";"SOIC16";"6-channel level shifter";"";
"X1";"2450AT18B100";"ANTENNA_JOHANSON_2500AT44M0400";"ANT_2500AT44M0400";"Johanson 2.3-2.7 GHz Chip Antenna";"";
